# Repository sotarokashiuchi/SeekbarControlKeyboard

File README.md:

# SeekbarControlKeyboard

## 概要
- シークバー(音楽の再生、停止、スキップなど)を制御するためのキーボード
- 5スイッチ、1ロータリーエンコーダ(ボタン付き)
- 分割キーボード対応
- LED対応
- 完全オープンで、各自発注可能

## デフォルトキーマップ
```
┌───┬───┬───┐
│ A │ B │ C │ // Aはロータリーエンコーダ
├───┼───┼───┤
│ D │ E │ F │
└───┴───┴───┘
```

| key | single tap         | double tap     | other action   |
| --- | ------------------ | -------------- | -------------- |
| A   |                    |                | 回転で音量調節 |
| B   | ファンクションキー |                |                |
| C   | デバイスをスリープ |                |                |
| D   | 少し戻る           | 前のトラックへ |                |
| E   | 一時停止/再生      |                |                |
| F   | 少し進む           | 次のトラックへ |                |

## 部品
| parts                      | counts | sample value(en) |
| -------------------------- | ------ | ---------------- |
| PCB                        | 1      | 88               |
| アクリル版                 | 1      | 310              |
| ProMicro                   | 1      | 770              |
| ダイオード                 | 6      | 10               |
| キースイッチ               | 5      | 350              |
| ロータリーエンコーダ(EC12) | 1      | 330              |
| PCBソケット                | 5      | 94               |
| タクトスイッチ             | 1      | 22               |
| M2ボルト(12.6mm以上)       | 4      |                  |
| M2ナット(2mm)              | 8      | 35               |
| -- options --              |        |                  |
| ノブ                       | 1      |                  |
| キーキャップ               | 5      |                  |
| M2ワッシャー(0.5mm)        | 8      | 15               |
| クッションゴム             | 4      |                  |
| LEDシート                  | 1      | 550              |
| ジャック線                 | 1      | 330              |
| TRRSジャック(MJ-4PP-9)     | 1      | 165              |
| total                      |        | 2167             |
| options total              |        | 1060             |

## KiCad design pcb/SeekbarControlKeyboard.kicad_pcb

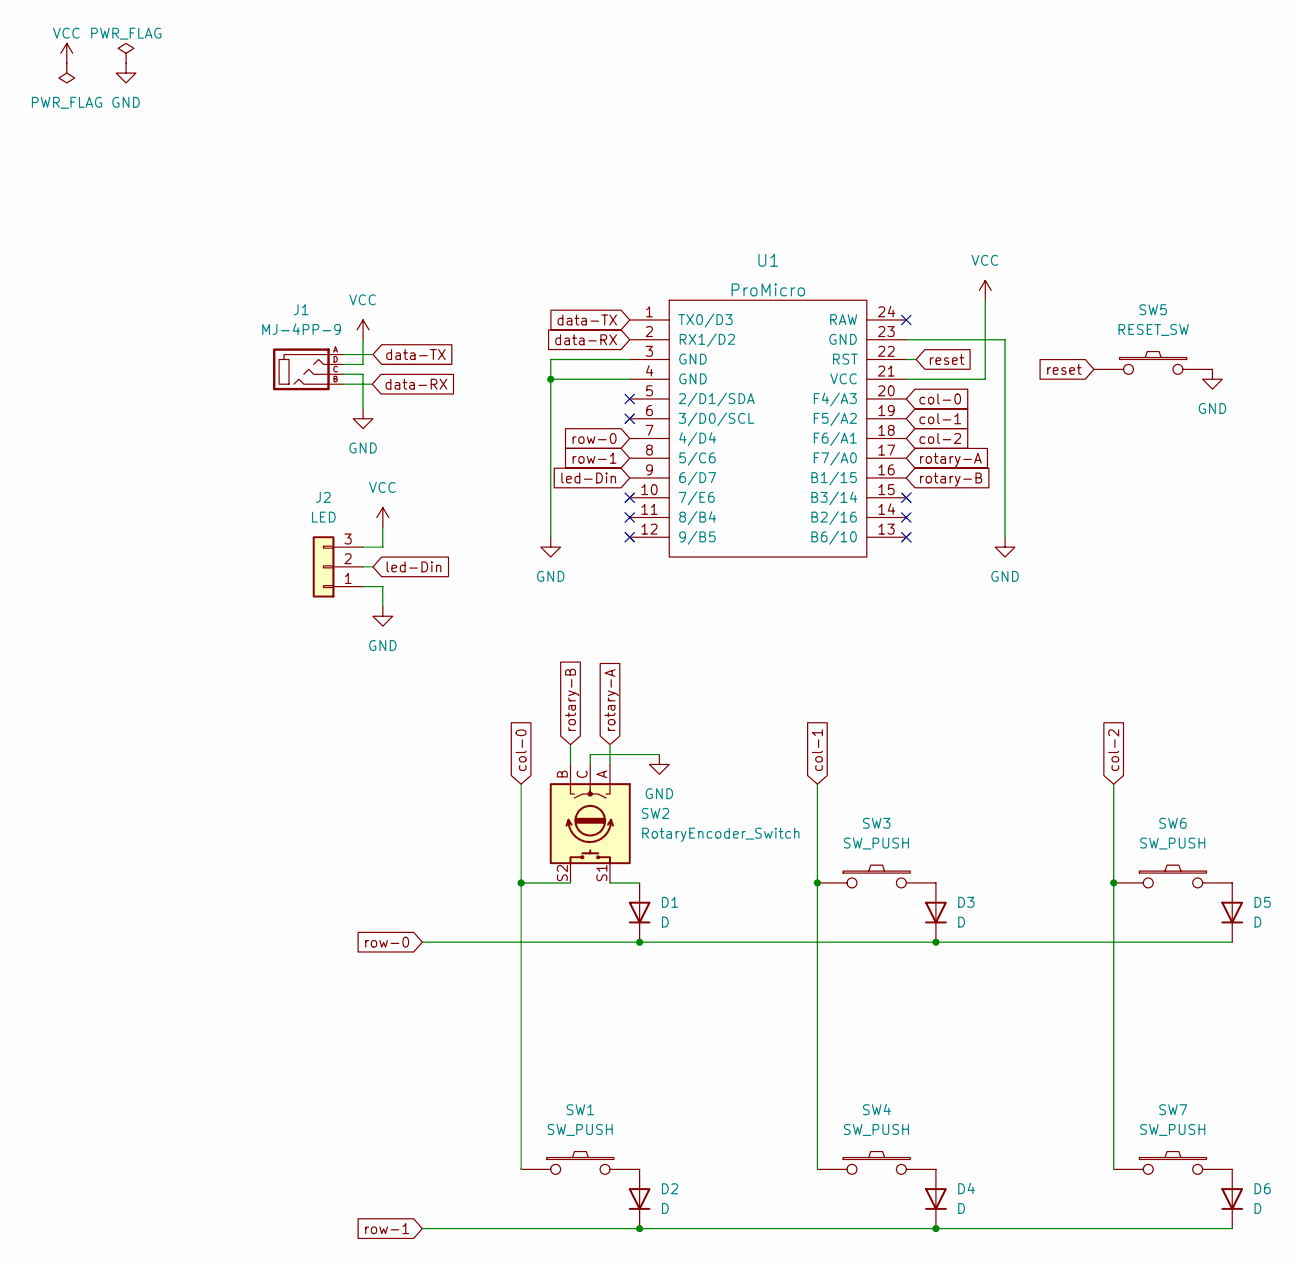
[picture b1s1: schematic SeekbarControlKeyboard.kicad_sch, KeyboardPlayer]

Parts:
D1, D2, D3, D4, D5, D6: D; D3_TH_SMD_v3
J1: MJ-4PP-9
J2: LED; StripLED_rev
SW1, SW3, SW4, SW6, SW7: SW_PUSH; CherryMX_Choc_Hotswap
SW2: RotaryEncoder_Switch; RotaryEncoder_EC11
SW5: RESET_SW; ResetSW
U1: ProMicro; ProMicro_v2

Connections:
GND: J1.C, J2.1, SW2.C, SW5.2, U1.3 (GND), U1.4 (GND), U1.23 (GND)
unnamed: D1.2 (A), SW2.S1
unnamed: D2.2 (A), SW1.2
unnamed: D3.2 (A), SW3.2
unnamed: D4.2 (A), SW4.2
unnamed: D5.2 (A), SW6.2
unnamed: D6.2 (A), SW7.2
VCC: J1.D, J2.3, U1.21 (VCC)
col-0: SW1.1, SW2.S2, U1.20 (F4/A3)
col-1: SW3.1, SW4.1, U1.19 (F5/A2)
col-2: SW6.1, SW7.1, U1.18 (F6/A1)
data-RX: J1.B, U1.2 (RX1/D2)
data-TX: J1.A, U1.1 (TX0/D3)
led-Din: J2.2, U1.9 (6/D7)
reset: SW5.1, U1.22 (RST)
rotary-A: SW2.A, U1.17 (F7/A0)
rotary-B: SW2.B, U1.16 (B1/15)
row-0: D1.1 (K), D3.1 (K), D5.1 (K), U1.7 (4/D4)
row-1: D2.1 (K), D4.1 (K), D6.1 (K), U1.8 (5/C6)

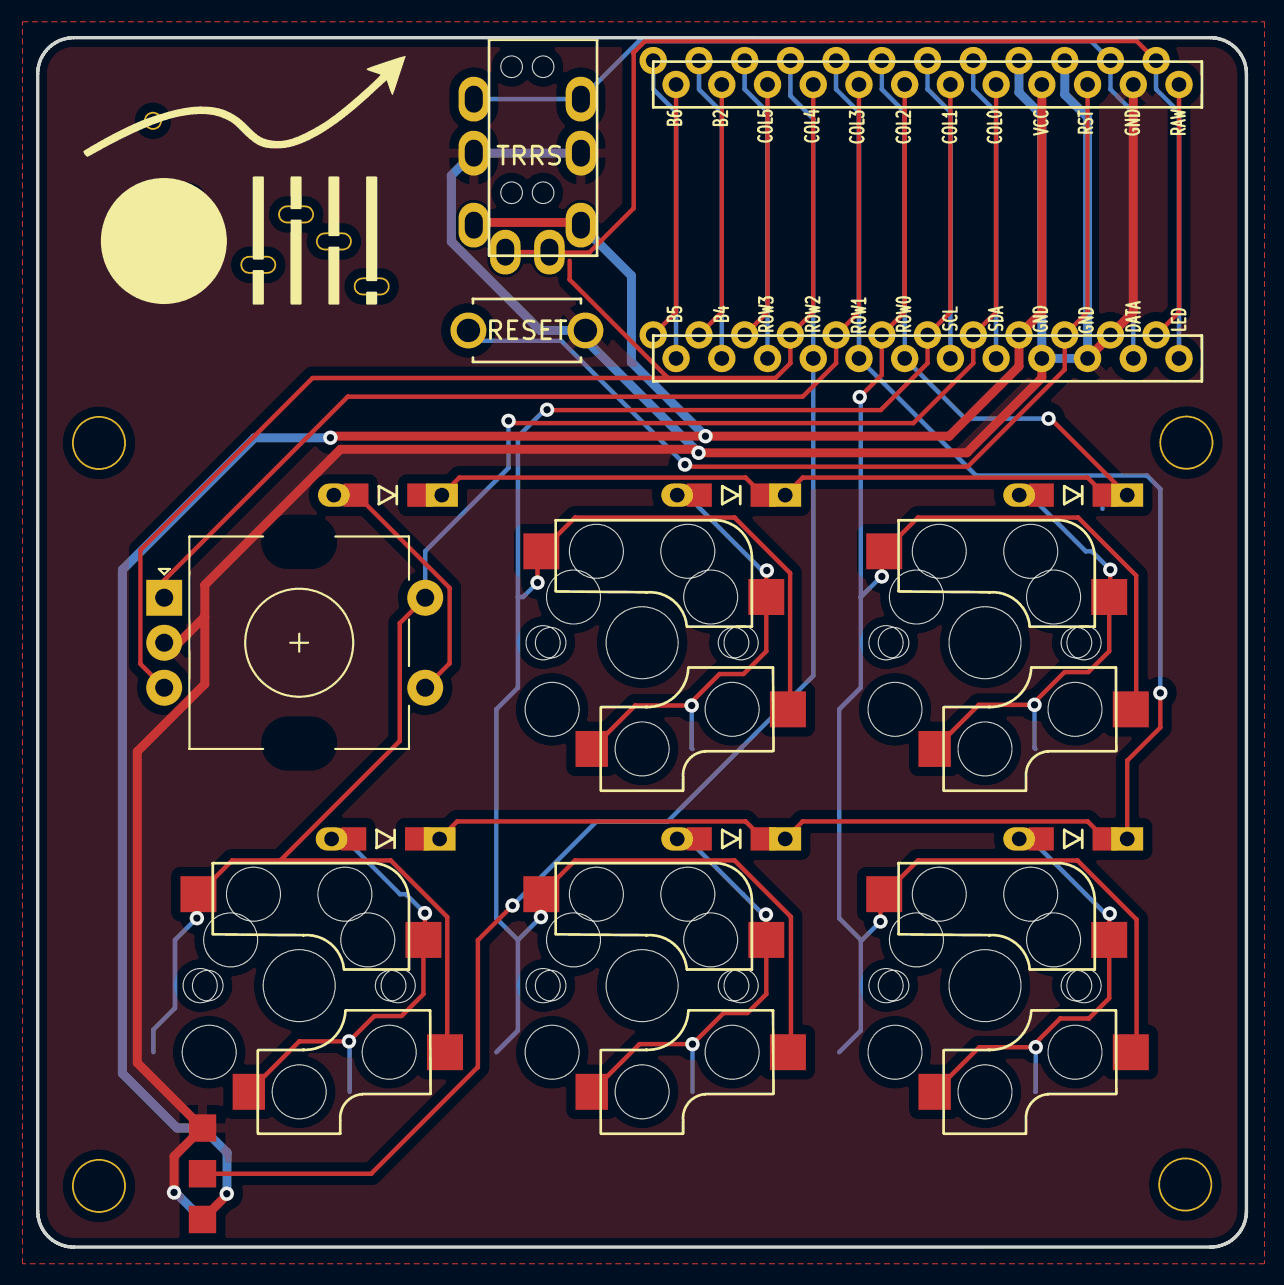
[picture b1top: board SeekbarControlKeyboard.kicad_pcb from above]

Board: 2 copper layers, 67.2 x 67.2 mm, 16 parts (0 on the bottom side), 19 nets.

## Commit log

2023-12-06 .gitignore
2023-12-06 first schematic
2023-12-06 footprint assignment
2023-12-11 complete PCB
2023-12-11 initilize keboard player
2023-12-12 complete SCD
2023-12-12 assingnment footpring of parts
2023-12-13 complete DRC
2023-12-13 add M2
2023-12-14 paint GND
2023-12-14 create logo
2023-12-14 fix Edge.Cuts
2023-12-14 finished version1.0
2023-12-15 PCB 発注
2023-12-15 rename file and folder
2023-12-15 create case file
2023-12-15 add case of keycap
2023-12-15 add case of rotary encoder
2023-12-16 finished plate of bottom and top
2023-12-16 parts list
2023-12-16 add parts list
2024-01-06 290mm*500mmのアクリル版用のデータを作成
2024-02-15 update case
2024-03-01 move folder
2024-03-01 fix M2 PCB close #2
2024-03-01 exchange rotary encoder and switch
2024-03-01 close #3
2024-03-01 add submodels
2024-03-01 chnage lib path
2024-03-03 move folder and fix Diode fotprint close #4
